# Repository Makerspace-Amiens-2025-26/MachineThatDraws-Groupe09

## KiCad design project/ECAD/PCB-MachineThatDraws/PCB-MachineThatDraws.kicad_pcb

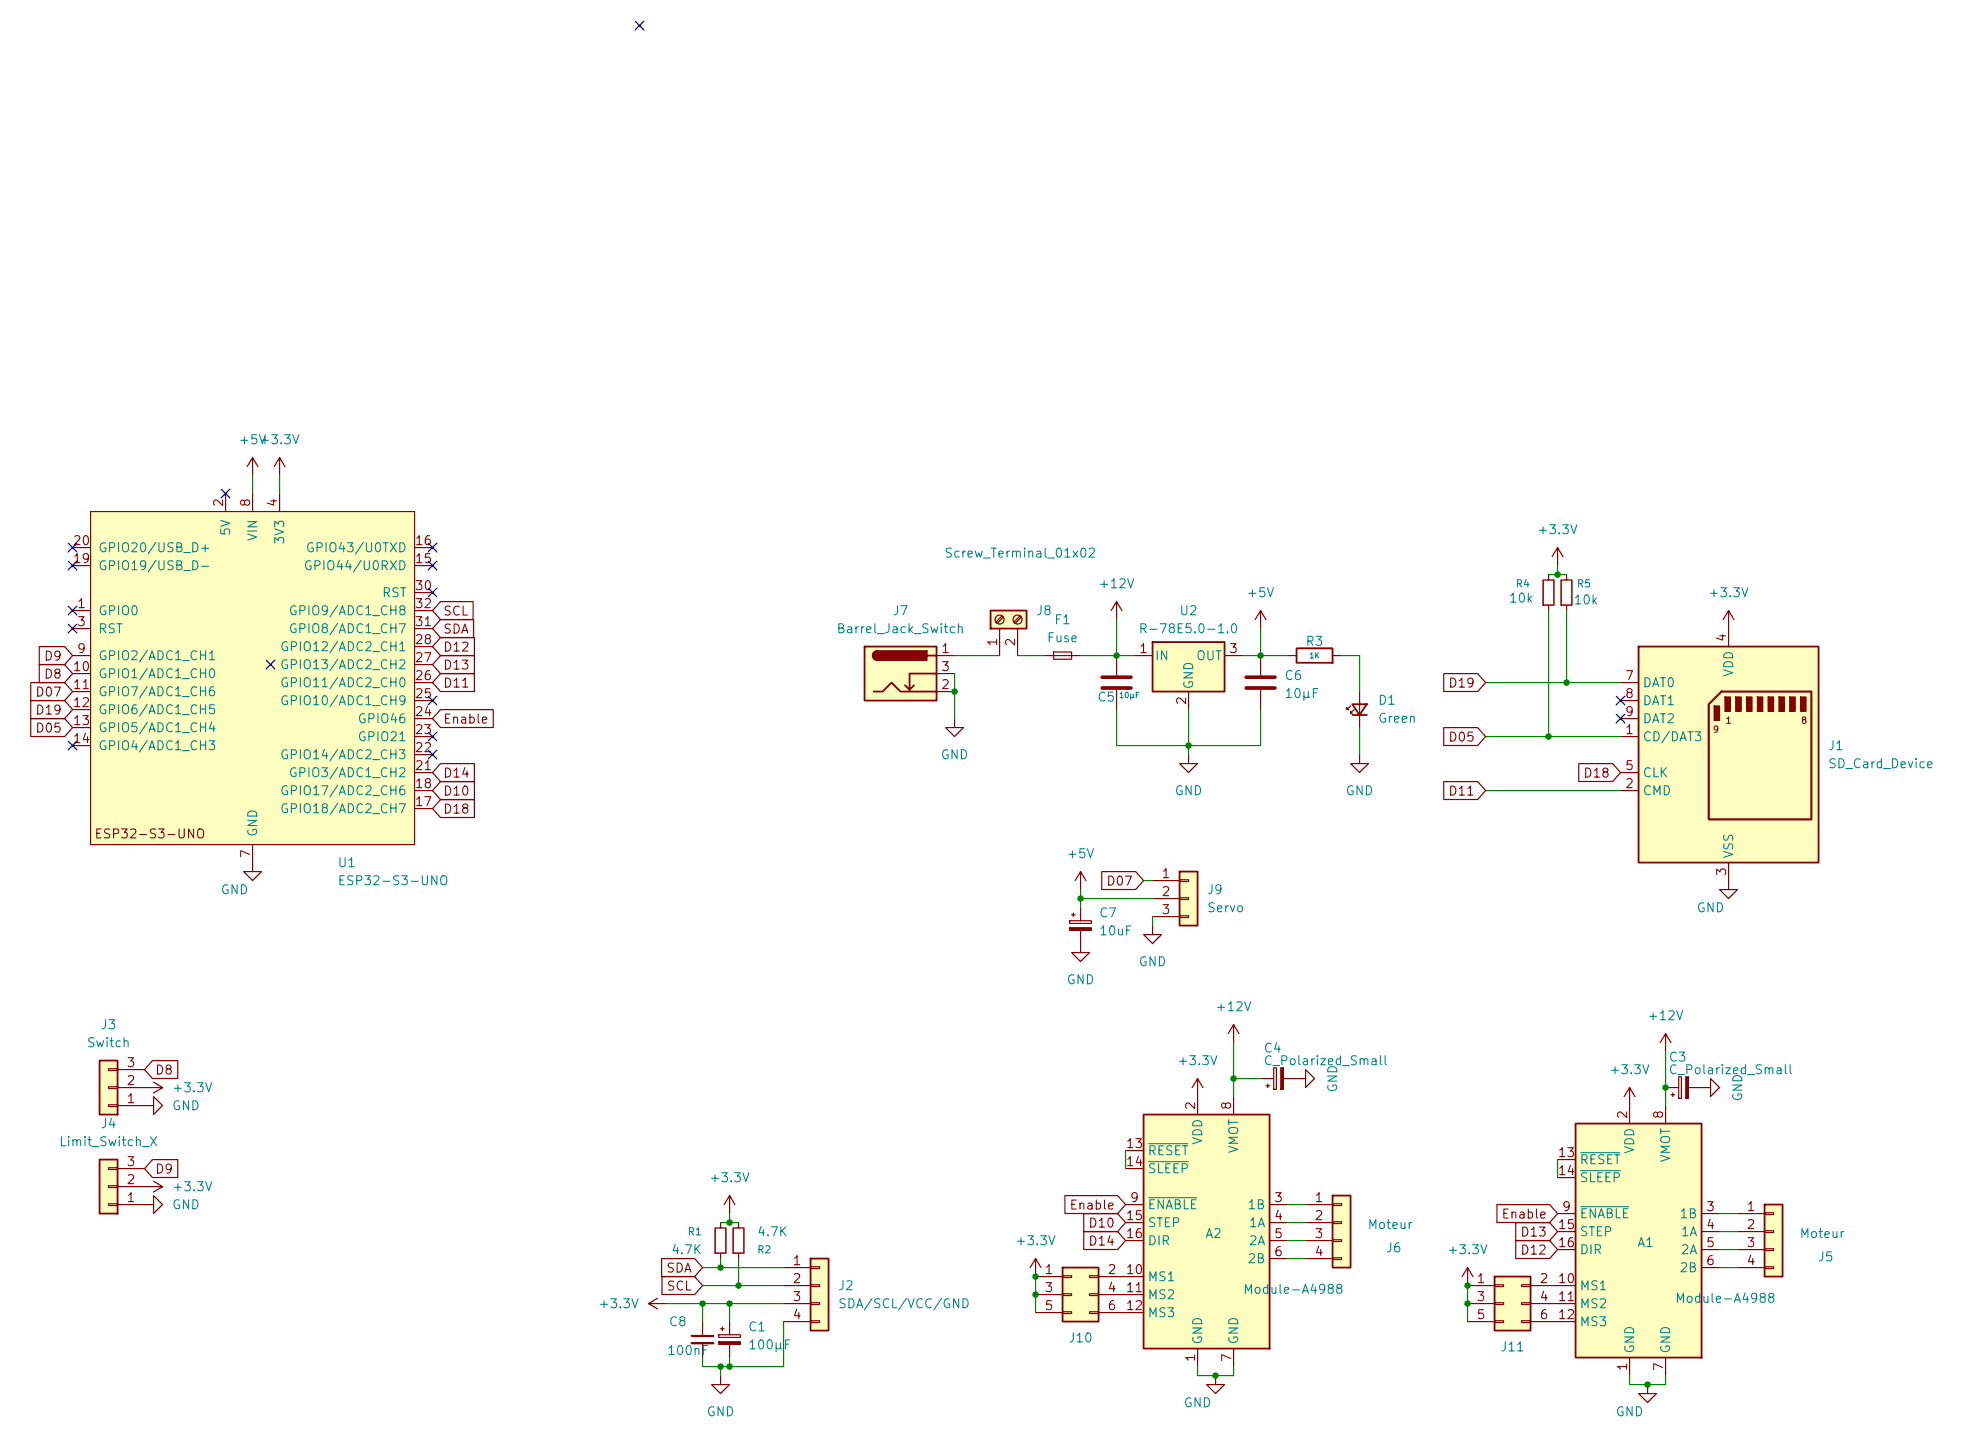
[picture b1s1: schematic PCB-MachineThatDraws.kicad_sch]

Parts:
A1, A2: Module-A4988; Pololu_Breakout-16_15.2x20.3mm
C1: 100µF; C_1206
C3, C4: C_Polarized_Small; CP_Elec_6.3x5.4
C5, C6: 10µF; C_1206
C7: 10uF; C_1206
C8: 100nF; C_1206
D1: Green; LED_1206_3216Metric
F1: Fuse; Fuseholder_Blade_Mini_Keystone_3568
J1: SD_Card_Device; SD_Hirose_DM1AA_SF_PEJ82
J2: SDA/SCL/VCC/GND; NS-Tech_Grove_1x04_P2mm_Vertical
J3: Switch; JST_PH_B3B-PH-K_1x03_P2.00mm_Vertical
J4: Limit_Switch_X; JST_PH_B3B-PH-K_1x03_P2.00mm_Vertical
J5, J6: Moteur; NS-Tech_Grove_1x04_P2mm_Vertical
J7: Barrel_Jack_Switch; BarrelJack_GCT_DCJ200-10-A_Horizontal
J8: Screw_Terminal_01x02; TerminalBlock_bornier-2_P5.08mm
J9: Servo; FanPinHeader_1x03_P2.54mm_Vertical
J10, J11: Conn_02x03_Odd_Even; PinHeader_2x03_P2.54mm_Vertical
R1, R2: 4.7K; R_1206
R3: 1K; R_1206
R4, R5: 10k; R_1206
U1: ESP32-S3-UNO; ESP_S3_UNO
U2: R-78E5.0-1.0; Converter_DCDC_RECOM_R-78E-0.5_THT

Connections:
+3.3V: A1.2 (VDD), A2.2 (VDD), C1.1, C8.1, J1.4 (VDD), J2.3, J3.2, J4.2, J10.1, J10.3, J10.5, J11.1, J11.3, J11.5, R1.2, R2.2, R4.2, R5.2, U1.4 (3V3)
+5V: C6.1, C7.1, J9.2, R3.1, U1.8 (VIN), U2.3 (OUT)
+12V: A1.8 (VMOT), A2.8 (VMOT), C3.1, C4.1, C5.1, F1.2, U2.1 (IN)
D05: J1.1 (CD/DAT3), R4.1, U1.13 (GPIO5/ADC1_CH4)
D07: J9.1, U1.11 (GPIO7/ADC1_CH6)
D8: J3.3, U1.10 (GPIO1/ADC1_CH0)
D9: J4.3, U1.9 (GPIO2/ADC1_CH1)
D10: A2.15 (STEP), U1.18 (GPIO17/ADC2_CH6)
D11: J1.2 (CMD), U1.26 (GPIO11/ADC2_CH0)
D12: A1.16 (DIR), U1.28 (GPIO12/ADC2_CH1)
D13: A1.15 (STEP), U1.27 (GPIO13/ADC2_CH2)
D14: A2.16 (DIR), U1.21 (GPIO3/ADC1_CH2)
D18: J1.5 (CLK), U1.17 (GPIO18/ADC2_CH7)
D19: J1.7 (DAT0), R5.1, U1.12 (GPIO6/ADC1_CH5)
Enable: A1.9 (~ENABLE), A2.9 (~ENABLE), U1.24 (GPIO46)
GND: A1.1 (GND), A1.7 (GND), A2.1 (GND), A2.7 (GND), C1.2, C3.2, C4.2, C5.2, C6.2, C7.2, C8.2, D1.1 (K), J1.3 (VSS), J1.6 (VSS), J2.4, J3.1, J4.1, J7.2, J7.3, J9.3, U1.6 (GND), U1.7 (GND), U1.29 (GND), U2.2 (GND)
unnamed: A1.4 (1A), J5.2
unnamed: A1.3 (1B), J5.1
unnamed: A1.5 (2A), J5.3
unnamed: A1.6 (2B), J5.4
unnamed: A1.10 (MS1), J11.2
unnamed: A1.11 (MS2), J11.4
unnamed: A1.12 (MS3), J11.6
unnamed: A1.13 (~RESET), A1.14 (~SLEEP)
unnamed: A2.4 (1A), J6.2
unnamed: A2.3 (1B), J6.1
unnamed: A2.5 (2A), J6.3
unnamed: A2.6 (2B), J6.4
unnamed: A2.10 (MS1), J10.2
unnamed: A2.11 (MS2), J10.4
unnamed: A2.12 (MS3), J10.6
unnamed: A2.13 (~RESET), A2.14 (~SLEEP)
unnamed: D1.2 (A), R3.2
unnamed: J7.1, J8.1
unnamed: F1.1, J8.2
SCL: U1.32 (GPIO9/ADC1_CH8)
SCL: J2.2, R2.1
SDA: J2.1, R1.1
SDA: U1.31 (GPIO8/ADC1_CH7)

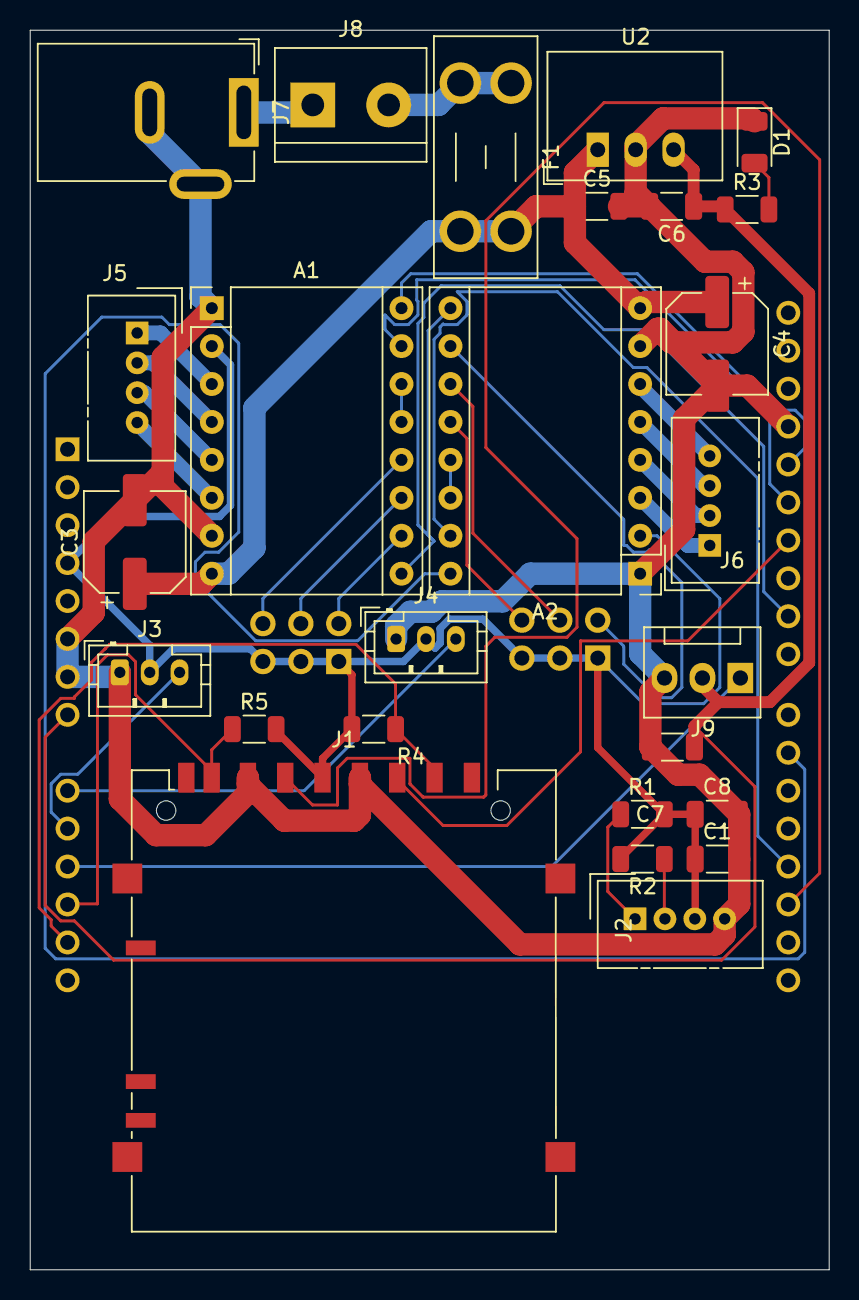
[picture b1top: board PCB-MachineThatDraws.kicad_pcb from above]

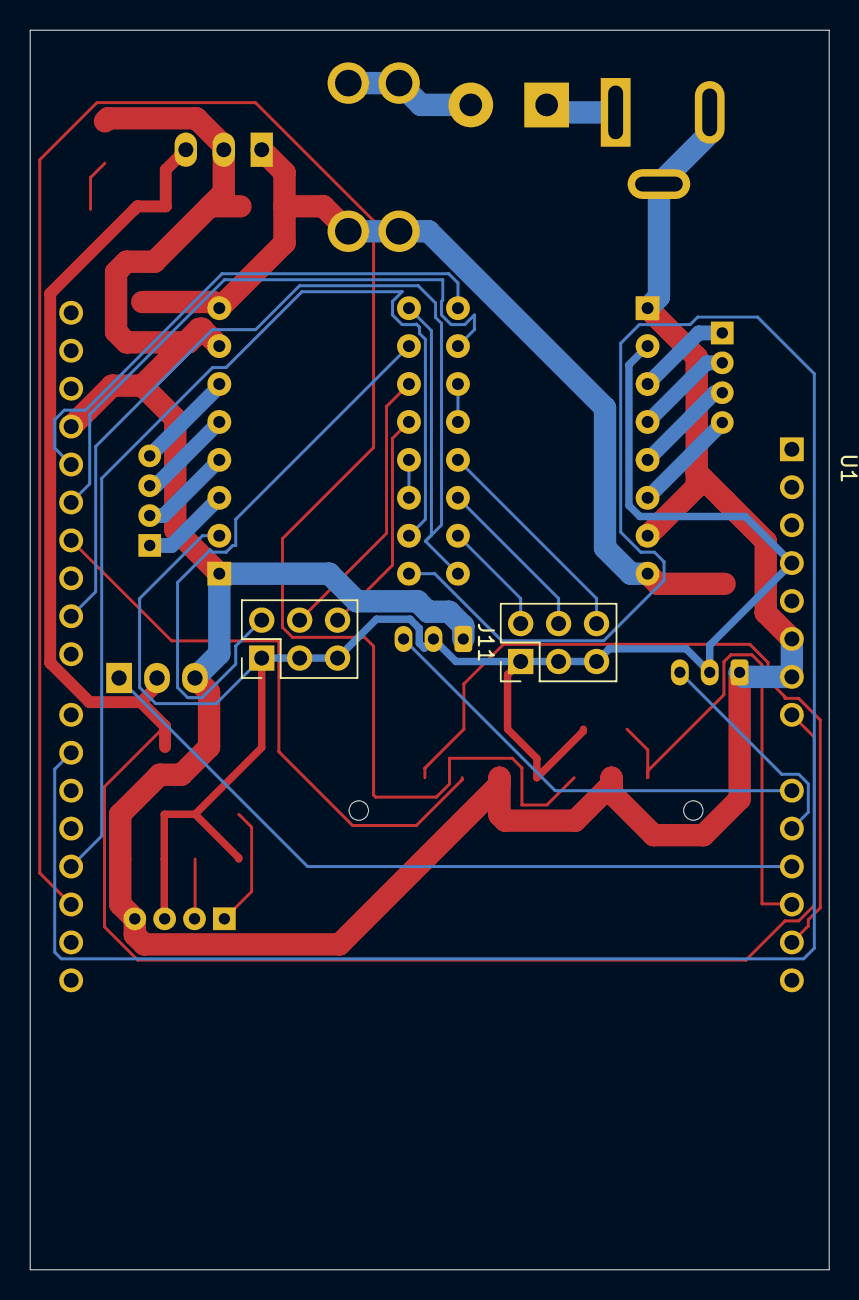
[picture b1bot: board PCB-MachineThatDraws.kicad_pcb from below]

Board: 2 copper layers, 53.5 x 83.0 mm, 29 parts (2 on the bottom side), 37 nets.

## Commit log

2026-01-06 Create _includes
2026-03-11 Rename videos1 (1) (1) (1) (1).mp4 to videos1.mp4
2026-03-20 first version
2026-03-20 cervo+regul5V
2026-04-03 pcb add
2026-04-10 Create #auto_saved_files#
2026-04-10 PCB up
2026-04-10 10-04
2026-04-21 pcb update
2026-04-22 maj pcb
2026-04-22 up pcb
2026-04-22 pcb import
